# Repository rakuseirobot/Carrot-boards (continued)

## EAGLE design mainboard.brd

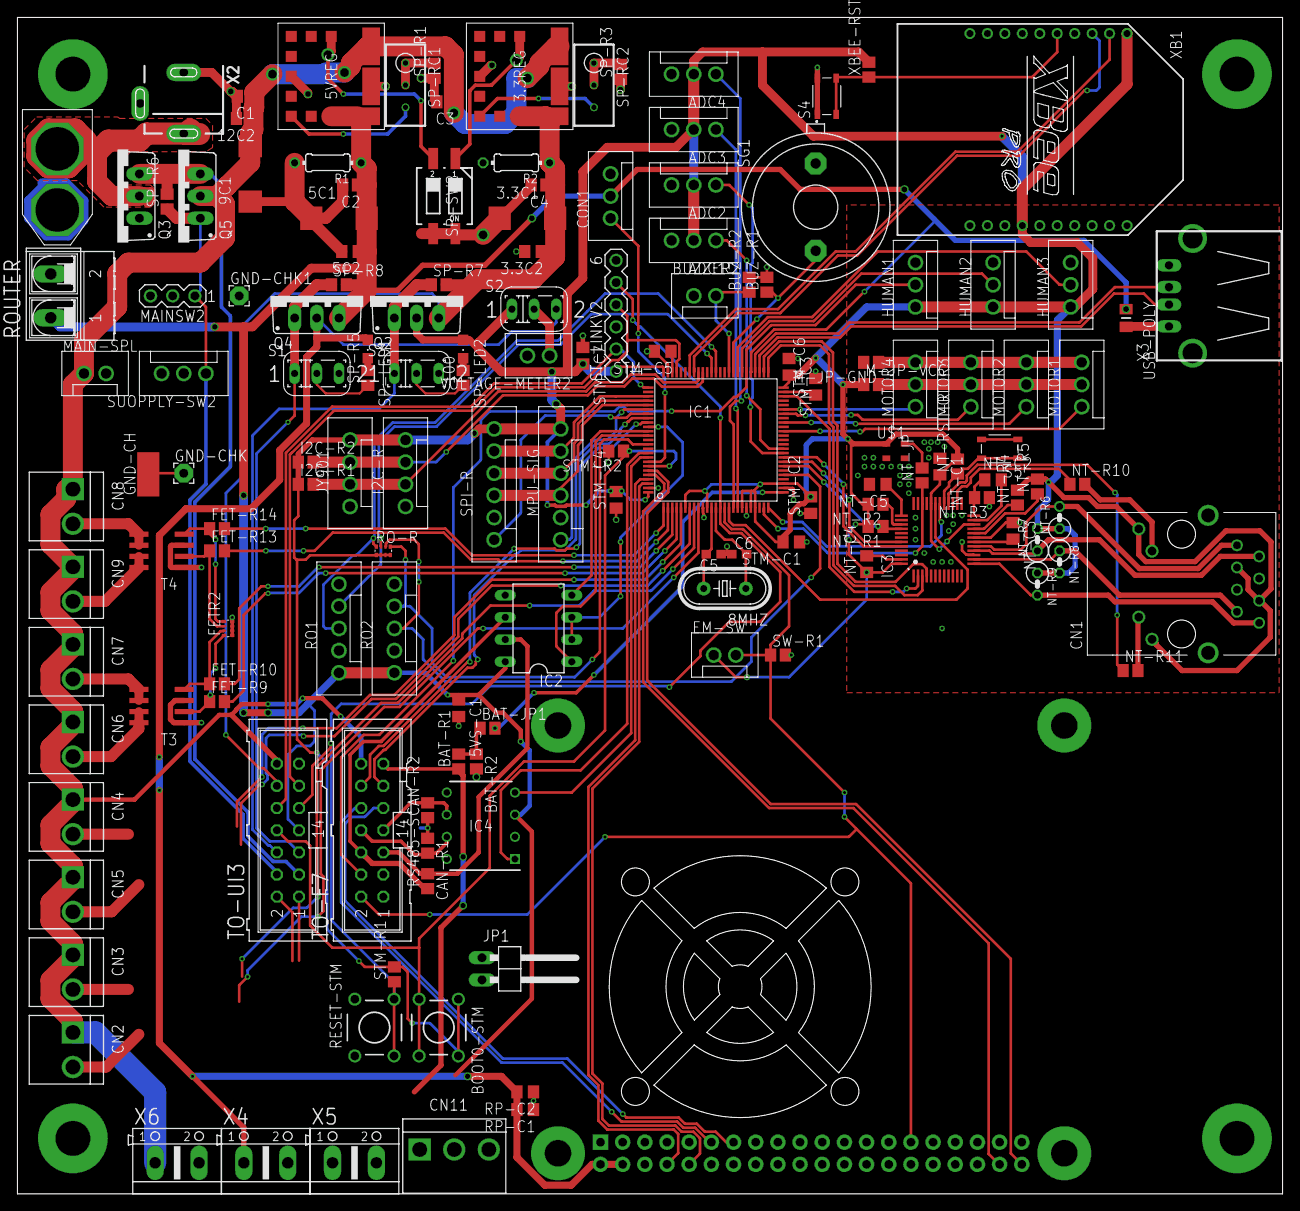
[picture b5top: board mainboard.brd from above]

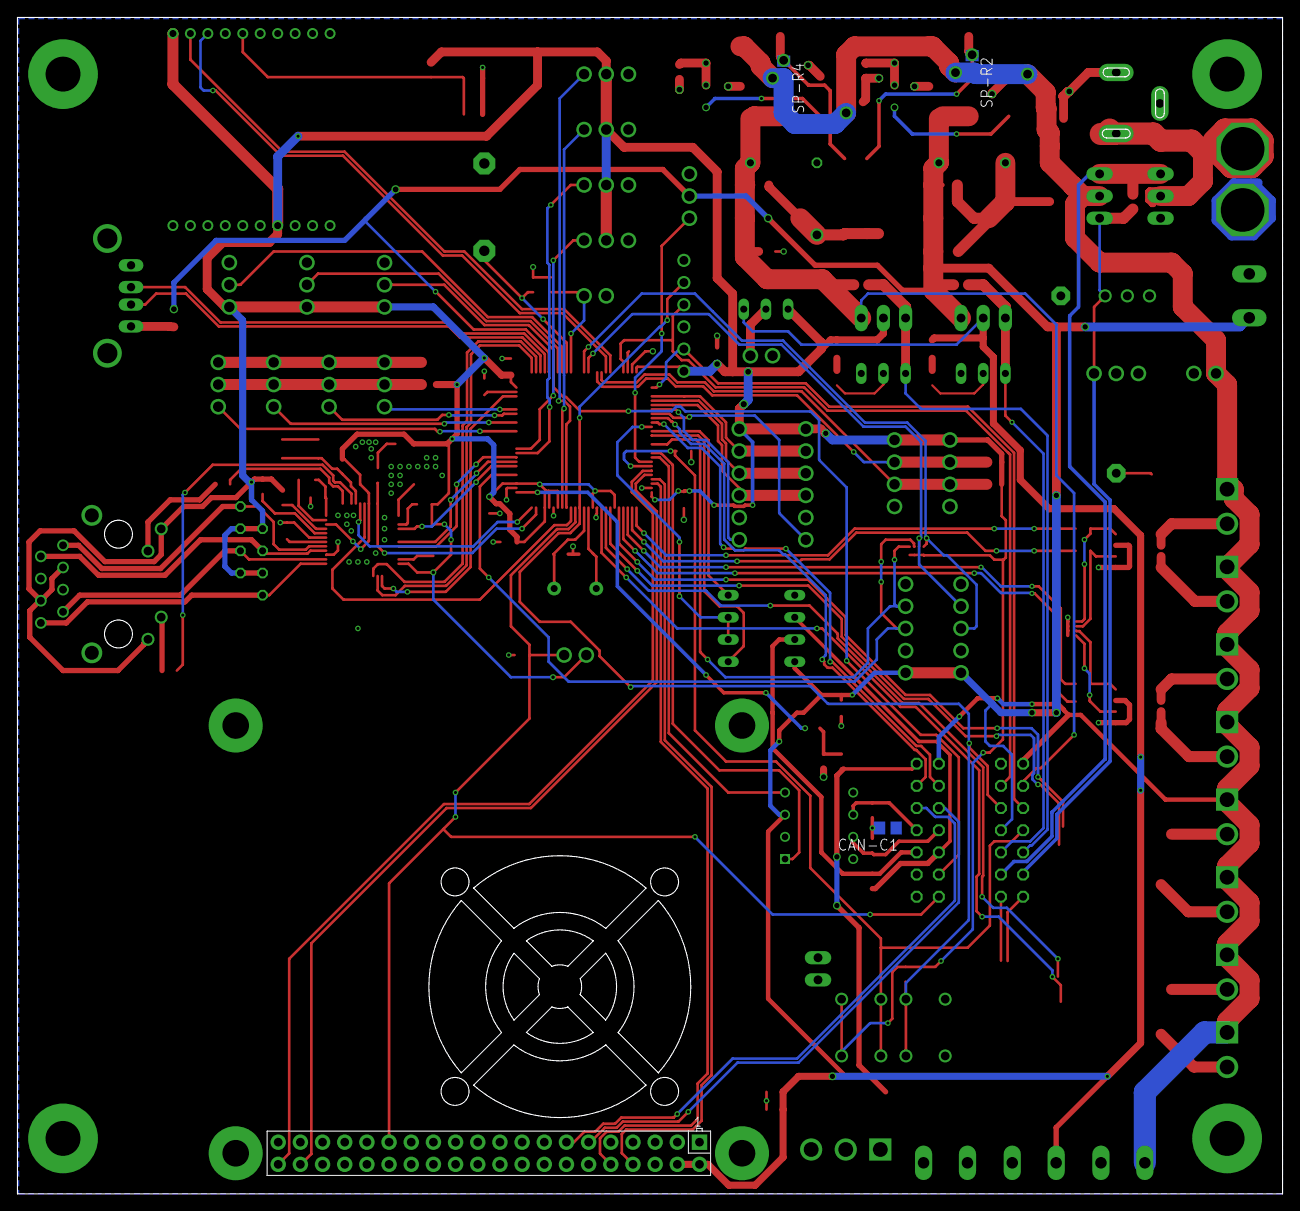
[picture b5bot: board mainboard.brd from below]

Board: 2 copper layers, 144.9 x 134.8 mm, 152 parts (4 on the bottom side), 122 nets.

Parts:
3.3C1, 5C1, 9C1: 100u; D/7343-31R
3.3C2, 5C2, 5VS-C1, 12C2: 0.1u; C0805
3.3REG, 5VREG: OKL-T_6-W12N-C; OKL-T/3-W5
8MHZ: P-08669_HUSG-12.000-20; HC49U-V
100: 330; R0805
ADC1, ADC2, ADC3, ADC4: XH-3; CON3
BAT-JP1: 0; R0805
BAT-R1: 2.2k; R0805
BAT-R2: 330; R0805
BOOT0-STM: DTS-6
BUZ-R1, BUZ-R2: 4.7k; R0805
BUZZER2: XH-2; CON2
C1, C3: 22uF25V; C2012
C2, C4: 10uF10V; C2012
C5, C6: 22pF; C1608
CAN-C1: 4.7u; C0805
CAN-R1, CAN-R2: 51; R0805
CN1: RJ45_PULSEJACK
CN2, CN3, CN4, CN5, CN6, CN7, CN8, CN9: B2P-VH
CN11: B3P-VH
CON1: XH-3; CON3
EM-SW: XH-2; CON2
FET-R9, FET-R10, FET-R13, FET-R14: 100; R0805
FETR2: 4.7k; EXBN8V
GND-CH: GND; SMD2,54-5,08
GND-CHK, GND-CHK1: GND; 2,15/1,0
HUMAN1, HUMAN2, HUMAN3: XH-3; CON3
I2C-R: XH-4; CON4
I2C-R1, I2C-R2: 4.7K; R0805
IC1: STM32F429VGT; LQFP100
IC2: LTC485N; DIL08
IC3: DP83848; LQFP48
IC4: MCP2561-E_P; DIP781W56P254L950H533Q8N
JP1: 1X02/90
JY901: XH-4; CON4
M-JP-GND: 0; R0805
M-JP-VCC: 0; R0805
MAIN-SPL: XH-2; CON2
MAINSW2: MAIN; MA03-1
MOTOR1, MOTOR2, MOTOR3, MOTOR4: XH-3; CON3
MPU-SIG: XH-6; CON6
NT-C1, NT-C2, NT-C3, NT-C4, NT-C5: 0.1u; C0805
NT-JP: 0; R0805
NT-R1, NT-R2, NT-R4, NT-R5: 2k; R0805
NT-R3: 4.87k; R0805
NT-R6, NT-R7, NT-R8, NT-R9: 51; 0207/2V
NT-R10, NT-R11: 330; R0805
NT-RST-R: 4.7K; R0805
Q2, Q3, Q4, Q5: IRF9530; TO220BV
R1, R2: 1.2k; 0204/7
RESET-STM: DTS-6
RO1, RO2: XH-5; CON5
RO-R: 4.7k; EXBN8V
ROUTER: AK500/2-H
RP-C1, RP-C2: 0.1u; C0805
RS485-S: 100; R0805
S1, S2, S3: VM; M251
S4, S5: SKRPACE010; SW_SKRPACE010
SG1: F/EE17P
SP-LED1, SP-LED2: CHIPLED_0805
SP-R1, SP-R3: 1.2k; R0805
SP-R2, SP-R4: 20K; R0805
SP-R5: 330; R0805
SP-R6, SP-R7, SP-R8: 4.7K; R0805
SP-RC1, SP-RC2: 20k; RTRIM3296W
SP-SW2: 219-02; CTS-219-02
SPI-R: XH-6; CON6
ST-LINKV2: MA06-1
STM-C1, STM-C2, STM-C3, STM-C4, STM-C5, STM-C6, STM-C7: 0.1u; C0805
STM-R1, STM-R2: 4.7K; R0805
SUOPPLY-SW2: XH-3; CON3
SW-R1: 4.7k; R0805
T3, T4: SO8
TO-F7: ML14
TO-UI3: ML14
U$1: ASE
U$2: XT60
USB-POLY: 400mA; F0805MP
VOLTAGE-METER2: XH-2; CON2
X1: RASPI_BOARD_B+#_FP; RASPI_BOARD_B+_FULL_PAD
X2: DCJACK-MJ179P; MJ-179P
X3: C-07674_USB-A; PN87520-S
X4, X5, X6: AK500/2
XB1: XBEE-PRO
XBEE-RST: 4.7K; R0805

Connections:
3V3-SW: Q2.G, S3.1, SP-R7.1, TO-UI3.6
5V-SW: Q4.G, S1.1, SP-R8.1, TO-UI3.5
12V-B: Q3.D, U$2.+, X2.1
12V-SW: MAINSW2.1, Q5.G, SP-R6.1, SUOPPLY-SW2.P$1, TO-UI3.4
+3V3: ADC1.P$2, ADC2.P$2, ADC3.P$2, ADC4.P$2, BOOT0-STM.1, BOOT0-STM.2, CN1.3, CN1.6, CN1.9, CN1.12, EM-SW.P$1, HUMAN1.P$1, HUMAN2.P$1, HUMAN3.P$1, I2C-R.P$4, I2C-R1.1, I2C-R2.1, IC1.6, IC1.11, IC1.19, IC1.21, IC1.22, IC1.28, IC1.50, IC1.75, IC1.100, IC3.22, IC3.32, IC3.48, JY901.P$4, M-JP-VCC.1, MPU-SIG.P$6, NT-C1.2, NT-C4.1, NT-R1.2, NT-R2.2, NT-R4.2, NT-R5.2, NT-R6.1, NT-R7.2, NT-R8.2, NT-R9.1, NT-RST-R.2, Q2.D, RO-R.1, RO-R.2, RO-R.3, RO-R.4, S2.1, SP-LED2.A, SPI-R.P$6, ST-LINKV2.1, STM-C1.2, STM-C2.2, STM-C3.2, STM-C4.2, STM-C7.2, STM-R1.2, U$1.4, X5.1, XB1.1, XB1.14, XBEE-RST.2
+3V3S: 3.3C1.+, 3.3C2.1, 3.3REG.4, 3.3REG.5, C4.1, Q2.S, R2.1, SP-R7.2, TO-UI3.12
+5V: Q4.D, RP-C1.2, RP-C2.2, S2.3, SP-LED1.A, X1.2, X1.4, X4.1
+5VS: 5C1.+, 5C2.1, 5VREG.4, 5VREG.5, 5VS-C1.1, C2.1, CON1.P$2, IC1.55, IC2.8, IC4.3, JP1.1, Q4.S, R1.1, RO1.P$1, RO2.P$1, ROUTER.1, SP-R8.2, TO-UI3.7, USB-POLY.1
+12V: 3.3REG.2, 5VREG.2, 9C1.+, 12C2.1, C1.1, C3.1, CN2.1, CN3.1, CN4.1, CN5.1, CN6.1, CN7.1, CN8.1, CN9.1, MAIN-SPL.P$1, Q5.D, SP-R2.2, SP-R4.2, TO-F7.14, TO-UI3.14, X6.1
+12VS: Q3.S, Q5.S, SP-R6.2, TO-UI3.3
ADC1: ADC1.P$1, IC1.36
ADC2: ADC2.P$1, IC1.35
ADC3: ADC3.P$1, IC1.18
ADC4: ADC4.P$1, IC1.17
BOOT0: BOOT0-STM.3, BOOT0-STM.4, IC1.94, STM-R2.1, TO-UI3.8
BOOT-RX: IC1.69, XB1.2
BOOT-TX: IC1.68, XB1.3
BUZZER1: BUZ-R1.1, IC1.59, SG1.1
BUZZER2: BUZ-R2.1, BUZZER2.P$2, IC1.60
CAN-H: CAN-R1.2, IC4.7, TO-F7.8
CAN-L: CAN-R2.2, IC4.6, TO-F7.7
CAN-RX: IC1.91, IC4.1
CAN-TX: IC1.92, IC4.4
EMERGENCY: EM-SW.P$2, IC1.15, SW-R1.1, TO-F7.2, X1.29
ETH_CRS_DV: IC1.32, IC3.40, NT-R1.1
ETH_MDC: IC1.16, IC3.31
ETH_MDIO: IC1.25, IC3.30
ETH_REF_CLK: IC1.24, IC3.34, NT-JP.1
ETH_RXD0: IC1.33, IC3.43
ETH_RXD1: IC1.34, IC3.44
ETH_TXD0: IC1.51, IC3.3
ETH_TXD1: IC1.52, IC3.4
ETH_TX_EN: IC1.48, IC3.2
F7-F4-SIG1: IC1.84, TO-F7.12
F7-F4-SIG2: IC1.83, TO-F7.11
F7-RS-SIG1: TO-F7.10, X1.11
F7-RS-SIG2: TO-F7.9, X1.13
FET5: FET-R9.2, IC1.4
FET6: FET-R10.2, IC1.3
FET7: FET-R13.2, IC1.2
FET8: FET-R14.2, IC1.1
GND: 3.3C1.-, 3.3C2.2, 3.3REG.3, 3.3REG.7, 5C1.-, 5C2.2, 5VREG.3, 5VREG.7, 5VS-C1.2, 9C1.-, 12C2.2, 100.1, ADC1.P$3, ADC2.P$3, ADC3.P$3, ADC4.P$3, BAT-R2.2, BUZ-R1.2, BUZ-R2.2, BUZZER2.P$1, C1.2, C2.2, C3.2, C4.2, C5.1, C6.1, CAN-C1.1, CN1.4, CN1.5, CN11.2, CON1.P$3, FETR2.1, FETR2.2, FETR2.3, FETR2.4, GND-CH.1, GND-CHK.1, GND-CHK1.1, HUMAN1.P$3, HUMAN2.P$3, HUMAN3.P$3, I2C-R.P$1, IC1.10, IC1.20, IC1.27, IC1.74, IC1.99, IC2.5, IC3.15, IC3.19, IC3.35, IC3.36, IC3.47, IC4.2, IC4.8, JP1.2, JY901.P$1, M-JP-GND.2, MAIN-SPL.P$2, MAINSW2.2, MPU-SIG.P$2, NT-C1.1, NT-C3.1, NT-C4.2, NT-C5.2, NT-R3.1, Q3.G, R1.2, R2.2, RESET-STM.1, RESET-STM.2, RO1.P$2, RO1.P$5, RO2.P$2, RO2.P$5, ROUTER.2, RP-C1.1, RP-C2.1, S1.2, S3.2, S4.1, S4.2, S5.3, S5.4, SG1.2, SP-R1.1, SP-R3.1, SP-R5.1, SP-SW2.3, SP-SW2.4, SPI-R.P$2, ST-LINKV2.3, STM-C1.1, STM-C2.1, STM-C3.1, STM-C4.1, STM-C5.2, STM-C6.2, STM-C7.1, STM-R2.2, SUOPPLY-SW2.P$2, SW-R1.2, T3.1, T3.3, T4.1, T4.3, TO-F7.1, TO-UI3.13, U$1.2, U$2.-, VOLTAGE-METER2.P$2, X1.6, X1.9, X1.14, X1.20, X1.25, X1.30, X1.34, X1.39, X2.2, X3.4, X3.S1, X3.S2, X4.2, X5.2, X6.2, XB1.10
HUMAN1: HUMAN1.P$2, IC1.56, TO-F7.4
HUMAN2: HUMAN2.P$2, IC1.57
HUMAN3: HUMAN3.P$2, IC1.58
LED5: CN6.2, T3.7, T3.8
LED6: CN7.2, T3.5, T3.6
LED7: CN9.2, T4.7, T4.8
LED8: CN8.2, T4.5, T4.6
LEDACT_LINK: IC3.26, NT-R10.1
LED_LINK: IC3.28, NT-R11.1
LIPO: BAT-R1.1, CN11.1, TO-F7.13, TO-UI3.1
LTC-SIG: IC1.85, IC2.2, IC2.3
MISO: IC1.79, MPU-SIG.P$4, SPI-R.P$4
MOSI: IC1.80, MPU-SIG.P$3, SPI-R.P$3
MOTOR-CH1: IC1.40, MOTOR1.P$1
MOTOR-CH2: IC1.42, MOTOR2.P$1
MOTOR-CH3: IC1.44, MOTOR3.P$1
MOTOR-CH4: IC1.45, MOTOR4.P$1
MOTOR-FET: CN11.3, TO-UI3.2
MPU-SIG: IC1.81, MPU-SIG.P$1
unnamed: IC1.73, STM-C5.1
unnamed: IC1.49, STM-C6.1
unnamed: SP-R1.2, SP-RC1.1, SP-RC1.2
unnamed: CAN-C1.2, CAN-R1.1, CAN-R2.1
unnamed: SP-LED1.C, SP-R5.2
unnamed: NT-JP.2, U$1.3
unnamed: SP-R3.2, SP-RC2.1, SP-RC2.2
unnamed: IC3.29, NT-RST-R.1, S5.1, S5.2
unnamed: 5VREG.6, SP-RC1.3
unnamed: IC3.23, NT-C2.2
unnamed: S2.2, VOLTAGE-METER2.P$1
unnamed: 3.3REG.6, SP-RC2.3
unnamed: 3.3REG.1, SP-R4.1, SP-SW2.1
unnamed: IC3.39, NT-R2.1
unnamed: IC3.21, NT-R4.1
unnamed: IC1.87, IC2.1
unnamed: IC1.86, IC2.4
unnamed: IC3.24, NT-C2.1, NT-R3.2
unnamed: IC3.20, NT-R5.1
unnamed: IC3.18, NT-C3.2
unnamed: 100.2, SP-LED2.C
unnamed: 8MHZ.1, C6.2, IC1.13
unnamed: 5VREG.1, SP-R2.1, SP-SW2.2
unnamed: BAT-JP1.2, IC1.26
unnamed: IC3.37, NT-C5.1
unnamed: 8MHZ.2, C5.2, IC1.12
unnamed: CN1.10, NT-R10.2
unnamed: CN1.11, NT-R11.2
unnamed: BAT-JP1.1, BAT-R1.2, BAT-R2.1
unnamed: M-JP-VCC.2, MOTOR1.P$2, MOTOR2.P$2, MOTOR3.P$2, MOTOR4.P$2
unnamed: M-JP-GND.1, MOTOR1.P$3, MOTOR2.P$3, MOTOR3.P$3, MOTOR4.P$3
unnamed: S4.3, S4.4, XB1.5, XBEE-RST.1
unnamed: USB-POLY.2, X3.1
unnamed: FET-R10.1, FETR2.7, T3.4
unnamed: FET-R9.1, FETR2.8, T3.2
unnamed: FET-R14.1, FETR2.5, T4.4
unnamed: FET-R13.1, FETR2.6, T4.2
NRST: IC1.14, RESET-STM.3, RESET-STM.4, ST-LINKV2.5, STM-R1.1, TO-UI3.9
PING: CON1.P$1, IC1.93
RD+: CN1.7, IC3.14, NT-R8.1
RD-: CN1.8, IC3.13, NT-R9.2
RO1-CHA: IC1.63, RO1.P$3, RO-R.8
RO1-CHB: IC1.64, RO1.P$4, RO-R.7
RO2-CHA: IC1.30, RO2.P$3, RO-R.6
RO2-CHB: IC1.89, RO2.P$4, RO-R.5
RPI-RX: IC1.97, X1.8
RPI-TX: IC1.98, X1.10
RS-CHA: IC2.6, RS485-S.1, TO-F7.6
RS-CHB: IC2.7, RS485-S.2, TO-F7.5
RS-SIG1: IC1.96, X1.38
RS-SIG2: IC1.95, X1.40
SCK: IC1.78, MPU-SIG.P$5, SPI-R.P$5
SCL: I2C-R.P$2, I2C-R1.2, IC1.67, JY901.P$2
SDA: I2C-R.P$3, I2C-R2.2, IC1.66, JY901.P$3
SPI-R-SS: IC1.82, SPI-R.P$1
SWCLK: IC1.76, ST-LINKV2.2, TO-UI3.10
SWDIO: IC1.72, ST-LINKV2.4, TO-UI3.11
TD+: CN1.1, IC3.17, NT-R6.2
TD-: CN1.2, IC3.16, NT-R7.1
USB-D+: IC1.54, X3.3
USB-D-: IC1.53, X3.2

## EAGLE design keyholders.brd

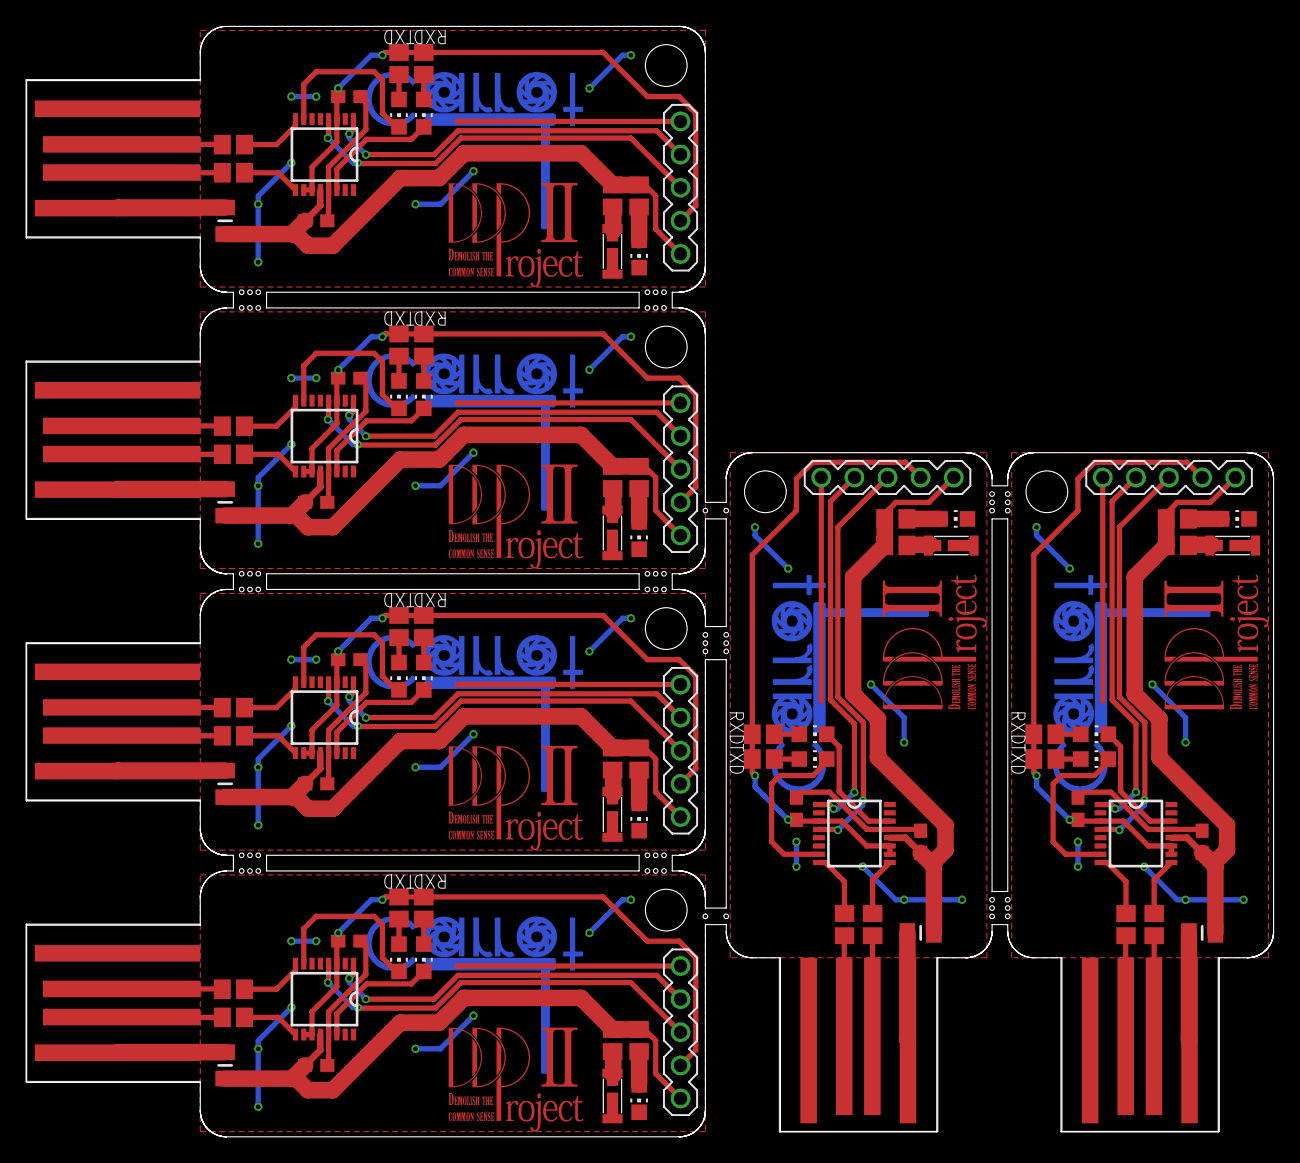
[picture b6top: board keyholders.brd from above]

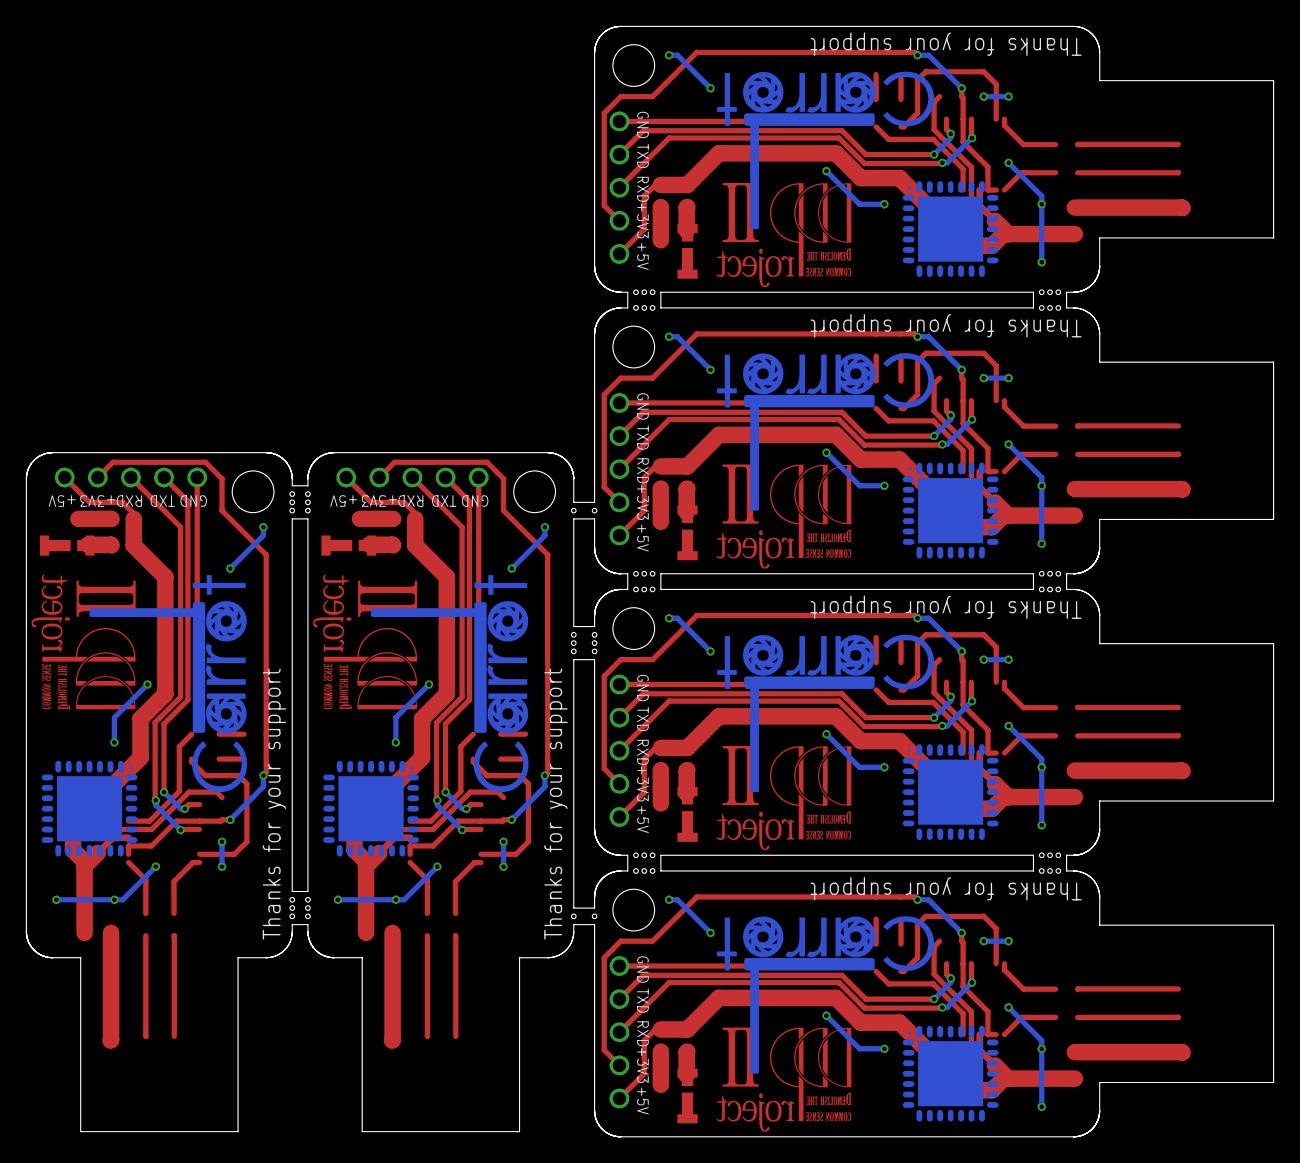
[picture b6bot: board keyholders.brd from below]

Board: 2 copper layers, 95.6 x 85.2 mm, 114 parts (12 on the bottom side), 108 nets.

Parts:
C1, C2, C3, C4, C5, C6, C7, C8, C9, C10, C11, C12: 0.1u; C1608
FT-R1, FT-R2, FT-R5, FT-R7, FT-R8, FT-R11, FT-R13, FT-R14, FT-R17, FT-R19, FT-R20, FT-R23, FT-R25, FT-R26, FT-R29, FT-R31, FT-R32, FT-R35: 330; R0805
FT-R3, FT-R4, FT-R9, FT-R10, FT-R15, FT-R16, FT-R21, FT-R22, FT-R27, FT-R28, FT-R33, FT-R34: 27; R0805
FT-R6, FT-R12, FT-R18, FT-R24, FT-R30, FT-R36: 100; R0805
IC1, IC4, IC6, IC8, IC10, IC12: LIS3LV02DQ; QFPN-28
IC2, IC3, IC5, IC7, IC9, IC11: FT230XS; SSOP16
LED1, LED2, LED3, LED4, LED5, LED6: CHIP-LED0805
RX-LED, RX-LED1, RX-LED2, RX-LED3, RX-LED4, RX-LED5: CHIP-LED0805
SV1, SV2, SV3, SV4, SV5, SV6: MA05-1
TX-LED, TX-LED1, TX-LED2, TX-LED3, TX-LED4, TX-LED5: CHIP-LED0805
U$1, U$2, U$9, U$13, U$17, U$21: USB-PAD; USB
U$3, U$4, U$10, U$14, U$18, U$22: I-05318_ＮＳＳＷ１５７Ｔ; NSSW157T
U$5, U$7, U$11, U$15, U$19, U$23: CARROT
U$6, U$8, U$12, U$16, U$20, U$24: DDPROJECT2-TOP
USB-POLY1, USB-POLY2, USB-POLY3, USB-POLY4, USB-POLY5, USB-POLY6: 350mA; F0805MP

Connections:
+3V3-FT: C2.1, FT-R1.2, FT-R2.2, IC3.3, IC3.10, IC3.11, SV1.2
+3V3-FT1: C4.1, FT-R7.2, FT-R8.2, IC2.3, IC2.10, IC2.11, SV2.2
+3V3-FT2: C6.1, FT-R13.2, FT-R14.2, IC5.3, IC5.10, IC5.11, SV3.2
+3V3-FT3: C8.1, FT-R19.2, FT-R20.2, IC7.3, IC7.10, IC7.11, SV4.2
+3V3-FT4: C10.1, FT-R25.2, FT-R26.2, IC9.3, IC9.10, IC9.11, SV5.2
+3V3-FT5: C12.1, FT-R31.2, FT-R32.2, IC11.3, IC11.10, IC11.11, SV6.2
GND: IC1.2, IC1.5, IC1.17
GND1: IC4.2, IC4.5, IC4.17
GND2: IC6.2, IC6.5, IC6.17
GND3: IC8.2, IC8.5, IC8.17
GND4: IC10.2, IC10.5, IC10.17
GND5: IC12.2, IC12.5, IC12.17
GNDA: C1.2, C2.2, IC3.5, IC3.13, LED3.C, SV1.5, U$2.GND, U$3.CATHODE
GNDA1: C3.2, C4.2, IC2.5, IC2.13, LED1.C, SV2.5, U$1.GND, U$4.CATHODE
GNDA2: C5.2, C6.2, IC5.5, IC5.13, LED2.C, SV3.5, U$9.GND, U$10.CATHODE
GNDA3: C7.2, C8.2, IC7.5, IC7.13, LED4.C, SV4.5, U$13.GND, U$14.CATHODE
GNDA4: C9.2, C10.2, IC9.5, IC9.13, LED5.C, SV5.5, U$17.GND, U$18.CATHODE
GNDA5: C11.2, C12.2, IC11.5, IC11.13, LED6.C, SV6.5, U$21.GND, U$22.CATHODE
unnamed: FT-R9.1, IC2.8
unnamed: FT-R10.1, IC2.9
unnamed: FT-R8.1, RX-LED1.A
unnamed: FT-R7.1, TX-LED1.A
unnamed: FT-R9.2, U$1.D+
unnamed: FT-R10.2, U$1.D-
unnamed: U$1.VCC, USB-POLY2.2
unnamed: FT-R11.1, LED1.A
unnamed: FT-R12.1, U$4.ANODE
unnamed: FT-R15.1, IC5.8
unnamed: FT-R16.1, IC5.9
unnamed: FT-R14.1, RX-LED2.A
unnamed: FT-R13.1, TX-LED2.A
unnamed: FT-R15.2, U$9.D+
unnamed: FT-R16.2, U$9.D-
unnamed: U$9.VCC, USB-POLY3.2
unnamed: FT-R17.1, LED2.A
unnamed: FT-R18.1, U$10.ANODE
unnamed: FT-R2.1, RX-LED.A
unnamed: FT-R1.1, TX-LED.A
unnamed: FT-R21.1, IC7.8
unnamed: FT-R3.2, U$2.D+
unnamed: FT-R3.1, IC3.8
unnamed: FT-R4.1, IC3.9
unnamed: FT-R4.2, U$2.D-
unnamed: FT-R22.1, IC7.9
unnamed: U$2.VCC, USB-POLY1.2
unnamed: FT-R5.1, LED3.A
unnamed: FT-R6.1, U$3.ANODE
unnamed: FT-R20.1, RX-LED3.A
unnamed: FT-R19.1, TX-LED3.A
unnamed: FT-R21.2, U$13.D+
unnamed: FT-R22.2, U$13.D-
unnamed: U$13.VCC, USB-POLY4.2
unnamed: FT-R23.1, LED4.A
unnamed: FT-R24.1, U$14.ANODE
unnamed: FT-R27.1, IC9.8
unnamed: FT-R28.1, IC9.9
unnamed: FT-R26.1, RX-LED4.A
unnamed: FT-R25.1, TX-LED4.A
unnamed: FT-R27.2, U$17.D+
unnamed: FT-R28.2, U$17.D-
unnamed: U$17.VCC, USB-POLY5.2
unnamed: FT-R29.1, LED5.A
unnamed: FT-R30.1, U$18.ANODE
unnamed: FT-R33.1, IC11.8
unnamed: FT-R34.1, IC11.9
unnamed: FT-R32.1, RX-LED5.A
unnamed: FT-R31.1, TX-LED5.A
unnamed: FT-R33.2, U$21.D+
unnamed: FT-R34.2, U$21.D-
unnamed: U$21.VCC, USB-POLY6.2
unnamed: FT-R35.1, LED6.A
unnamed: FT-R36.1, U$22.ANODE
RXD: IC3.4, SV1.3
RXD1: IC2.4, SV2.3
RXD2: IC5.4, SV3.3
RXD3: IC7.4, SV4.3
RXD4: IC9.4, SV5.3
RXD5: IC11.4, SV6.3
RXLED: IC3.14, RX-LED.C
RXLED1: IC2.14, RX-LED1.C
RXLED2: IC5.14, RX-LED2.C
RXLED3: IC7.14, RX-LED3.C
RXLED4: IC9.14, RX-LED4.C
RXLED5: IC11.14, RX-LED5.C
TXD: IC3.1, SV1.4
TXD1: IC2.1, SV2.4
TXD2: IC5.1, SV3.4
TXD3: IC7.1, SV4.4
TXD4: IC9.1, SV5.4
TXD5: IC11.1, SV6.4
TXLED: IC3.7, TX-LED.C
TXLED1: IC2.7, TX-LED1.C
TXLED2: IC5.7, TX-LED2.C
TXLED3: IC7.7, TX-LED3.C
TXLED4: IC9.7, TX-LED4.C
TXLED5: IC11.7, TX-LED5.C
V+: C1.1, FT-R5.2, FT-R6.2, IC3.12, SV1.1, USB-POLY1.1
V+1: C3.1, FT-R11.2, FT-R12.2, IC2.12, SV2.1, USB-POLY2.1
V+2: C5.1, FT-R17.2, FT-R18.2, IC5.12, SV3.1, USB-POLY3.1
V+3: C7.1, FT-R23.2, FT-R24.2, IC7.12, SV4.1, USB-POLY4.1
V+4: C9.1, FT-R29.2, FT-R30.2, IC9.12, SV5.1, USB-POLY5.1
V+5: C11.1, FT-R35.2, FT-R36.2, IC11.12, SV6.1, USB-POLY6.1
VDD: IC1.3, IC1.19
VDD1: IC4.3, IC4.19
VDD2: IC6.3, IC6.19
VDD3: IC8.3, IC8.19
VDD4: IC10.3, IC10.19
VDD5: IC12.3, IC12.19

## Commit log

2019-06-06 #first
2019-06-06 #update
2019-06-08 #OTL 意外とやること多い
2019-06-09 #update UI,F7 だいたい完成 #todo シルク
2019-06-09 #update UI,F7 シルク官僚
2019-06-17 #早く仕上げろー
2019-06-18 #update 大体完成 由利倫見れたら見てw
2019-06-19 #完成くらい
2019-06-19 #update ほぼ完成、F7,UI,KeyHolder基板ガーバ出力済み、main基板はあとはベタ確認とシルク最終チェック。明日の夜発注する！
2019-06-20 #update UI teardrop メイン 少しベタ切った
2019-06-20 #update ベタ切り、シルク調整
2019-06-20 #update 塾から帰ってきたら、teardropしてCAMして八(*´ε`*)ﾁｭｯﾁｭ
2019-06-20 #finish 発注しました
2019-06-23 #update 部品リスト
2019-06-29 #finish 部品発注完了
